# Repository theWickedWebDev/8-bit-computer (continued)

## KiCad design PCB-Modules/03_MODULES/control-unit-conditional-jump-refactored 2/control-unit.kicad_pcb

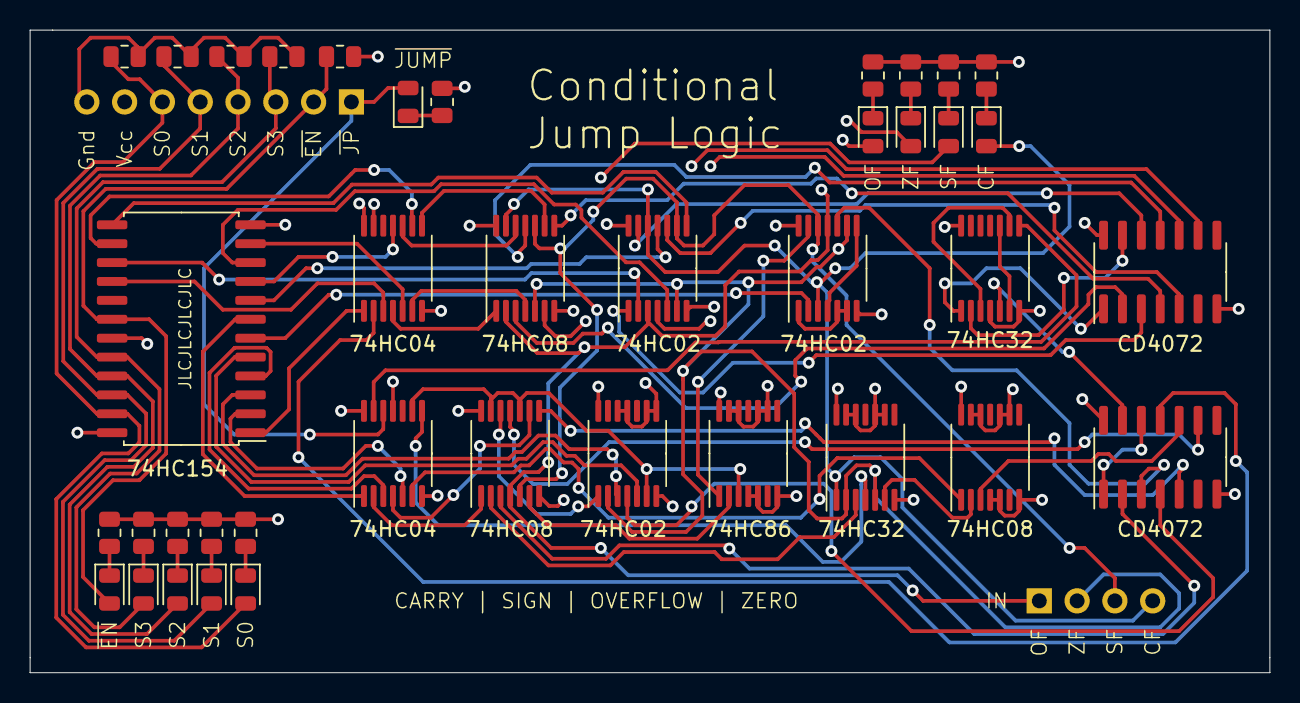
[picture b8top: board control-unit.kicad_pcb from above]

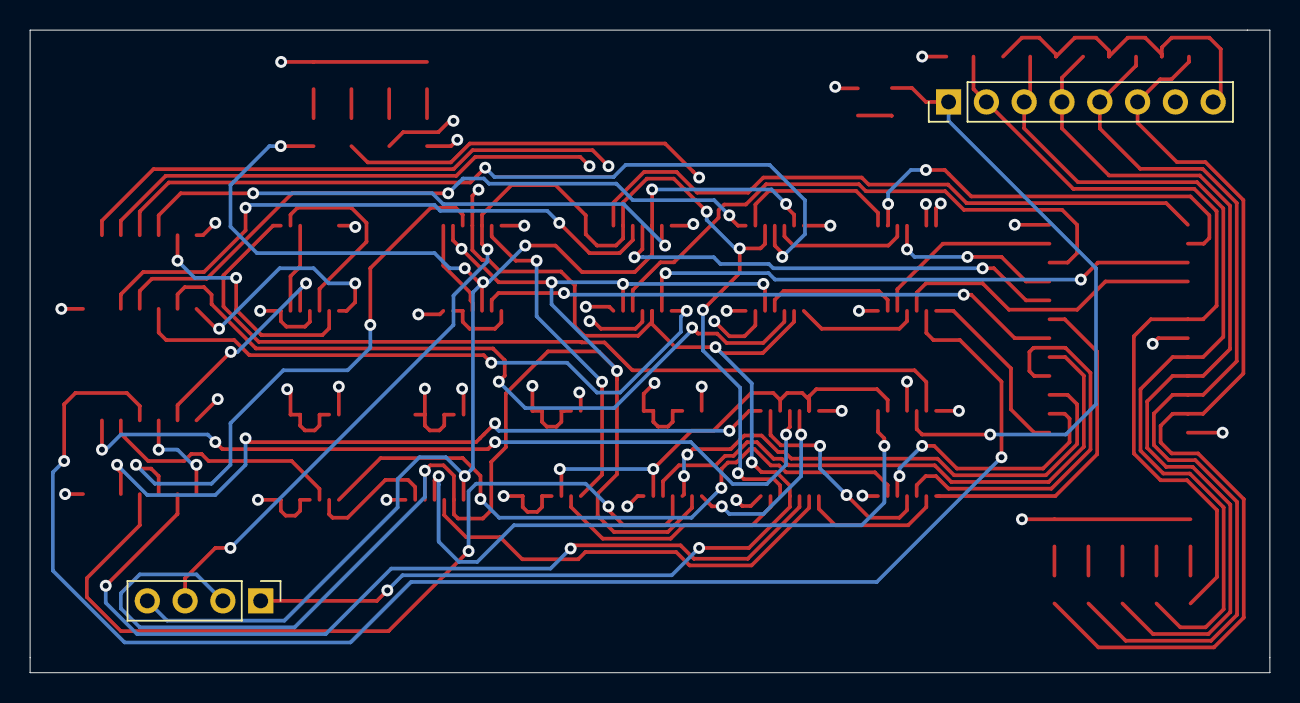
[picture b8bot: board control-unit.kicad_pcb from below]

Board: 4 copper layers, 83.3 x 43.2 mm, 41 parts (2 on the bottom side), 75 nets.

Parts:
D1, D2, D3, D4, D5, D6, D7, D8, D9, D10: LED; LED_0805_2012Metric
J3: Conn_01x08; PinHeader_1x08_P2.54mm_Vertical
J4: Conn_01x04; PinHeader_1x04_P2.54mm_Vertical
R1, R2, R3, R4, R5, R6, R7, R8, R9, R10, R11, R12, R13, R14, R15: R_US; R_0805_2012Metric
U1, U4: 74LS04; TSSOP-14_4.4x5mm_P0.65mm
U2, U5, U9: 74LS02; TSSOP-14_4.4x5mm_P0.65mm
U3, U6, U14: 74LS08; TSSOP-14_4.4x5mm_P0.65mm
U7, U12: 74LS32; TSSOP-14_4.4x5mm_P0.65mm
U8: 74LS86; TSSOP-14_4.4x5mm_P0.65mm
U10, U11: CD4072; SOIC-14_3.9x8.7mm_P1.27mm
U13: 74LS154; SOIC-24W_7.5x15.4mm_P1.27mm

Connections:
ADR0: D6.2, J3.6, R11.1, U13.23
ADR1: D7.2, J3.5, R12.1, U13.22
ADR2: D8.2, J3.4, R13.1, U13.21
ADR3: D9.2, J3.3, R14.1, U13.20
CARRY_FLAG: D2.2, J4.4, U2.12, U3.13, U5.3, U7.1
EN: D10.2, J3.2, R15.1, U13.18
GND: J3.8, R1.2, R2.2, R3.2, R4.2, R5.2, R6.2, R7.2, R8.2, R9.2, R10.2, R11.2, R12.2, R13.2, R14.2, U1.7, U1.13, U2.7, U3.7, U4.7, U4.11, U5.7, U6.7, U7.7, U7.9, U7.10, U7.12, U7.13, U8.4, U8.5, U8.7, U8.9, U8.10, U8.12, U8.13, U9.7, U9.8, U9.9, U9.11, U9.12, U10.7, U11.7, U12.4, U12.7, U13.12, U13.19, U14.4, U14.5, U14.7, U14.9, U14.10, U14.12, U14.13
LOAD_PROGRAM_COUNTER_COND: D1.2, J3.1, U4.12
unnamed: D1.1, R1.1
unnamed: D2.1, R2.1
unnamed: D3.1, R3.1
unnamed: D4.1, R4.1
unnamed: D5.1, R5.1
unnamed: D6.1, R6.1
unnamed: D7.1, R7.1
unnamed: D8.1, R8.1
unnamed: D9.1, R9.1
unnamed: D10.1, R10.1
unnamed: U1.4, U3.1
unnamed: U1.6, U3.4
unnamed: U1.8, U3.9
unnamed: U1.10, U3.12
unnamed: U4.2, U6.1
unnamed: U4.4, U6.9
unnamed: U4.8, U7.4
unnamed: U5.1, U5.5, U5.6
unnamed: U5.4, U5.8
unnamed: U5.13, U8.1
unnamed: U6.2, U7.3
unnamed: U6.6, U8.2
unnamed: U6.12, U9.1
unnamed: U10.1, U12.1
unnamed: U10.13, U12.2
unnamed: U11.1, U11.12
unnamed: U11.13, U12.5
unnamed: U12.3, U12.9
unnamed: U4.13, U12.8
unnamed: U12.6, U12.10
unnamed: U4.6, U14.1
unnamed: U7.6, U14.2
OR_JA_JNBE: U5.10, U11.3
OR_JBE_JNA: U6.3, U11.2
OR_JB_JNAE_JC: U3.11, U10.11
OR_JE_JZ: U3.6, U10.9
OR_JGE_JNL: U6.8, U11.5
OR_JG_JNLE: U6.11, U11.9
OR_JLE_JNG: U11.10, U14.3
OR_JL_JNGE: U9.4, U11.4
OR_JNB_JAE_JNC: U2.13, U10.12
OR_JNE_JNZ: U2.4, U10.10
OR_JNO: U2.1, U10.3
OR_JNS: U2.10, U10.5
OR_JO: U3.3, U10.2
OR_JS: U3.8, U10.4
OR_JUMP: U1.2, U11.11
OVERFLOW_FLAG: D5.2, J4.1, U2.3, U3.2, U5.11, U6.4
SF=OF: U4.9, U6.10, U6.13, U8.3, U9.6
SIGN_FLAG: D3.2, J4.3, U2.9, U3.10, U5.12, U6.5
VCC: J3.7, R15.2, U1.14, U2.14, U3.14, U4.14, U5.14, U6.14, U7.14, U8.14, U9.14, U10.14, U11.14, U12.14, U13.24, U14.14
ZERO_FLAG: D4.2, J4.2, U2.6, U3.5, U5.9, U7.2, U7.5, U9.2
~J: U1.1, U13.1
~JA_JNBE: U5.2, U13.6
~JBE_JNA: U4.1, U13.7
~JB_JNAE_JC: U1.11, U13.9
~JE_JZ: U1.5, U13.11
~JGE_JNL: U4.3, U13.4
~JG_JNLE: U9.3, U13.3
~JLE_JNG: U4.5, U13.2
~JL_JNGE: U9.5, U13.5
~JNB_JAE_JNC: U2.11, U13.8
~JNE_JNZ: U2.5, U13.10
~JNO: U2.2, U13.15
~JNS: U2.8, U13.13
~JO: U1.3, U13.16
~JS: U1.9, U13.14
